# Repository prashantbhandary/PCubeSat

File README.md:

# PocketQube PCB

KiCad schematic and PCB for the electronics of a 1.5U PocketQube educational satellite model.

## Paper
This project is described in a technical report:
**Electronics Design of a Low-Cost 1.5U PocketQube Educational Satellite Model with LoRa Telemetry and Stacked PCBs** — **Prashant Bhandari**, 2026. [Read the paper](https://www.researchgate.net/publication/418425160) · DOI: [10.13140/RG.2.2.14744.84482](https://doi.org/10.13140/RG.2.2.14744.84482)

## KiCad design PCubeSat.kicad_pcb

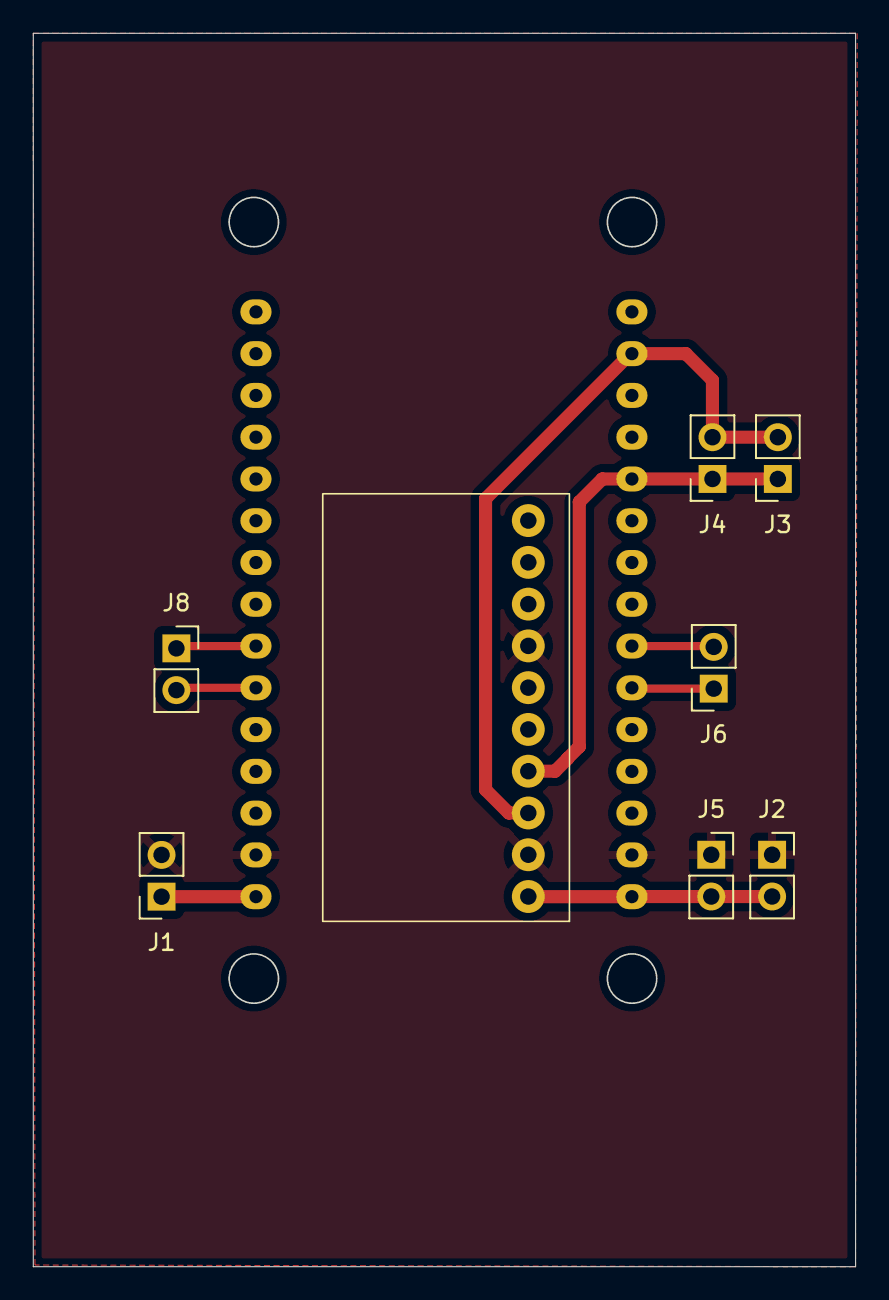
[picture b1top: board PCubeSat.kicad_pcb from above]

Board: 2 copper layers, 50.0 x 75.0 mm, 9 parts (1 on the bottom side), 9 nets.

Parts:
J1, J2, J3, J4, J5, J6, J8: Conn_01x02_Pin; PinSocket_1x02_P2.54mm_Vertical
U1: ESP32-WROOM-32E-N8R2; ESP_Test
U2: mpu9250

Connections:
/3V3: J2.2, J5.2, U1.16 (3V3), U2.1 (VCC)
/GND: J1.2, J2.1, J5.1, U1.14 (GND), U1.17 (GND), U2.2 (GND), U2.7 (AD0)
/IO21: J3.1, J4.1, U1.26 (IO21), U2.4 (SDA)
/IO22: J3.2, J4.2, U1.29 (IO22), U2.3 (SCL)
/VIN: J1.1, U1.15 (VIN)
unnamed: J6.1, U1.21 (IO16)
unnamed: J6.2, U1.22 (IO17)
unnamed: J8.1, U1.9 (IO26)
unnamed: J8.2, U1.10 (IO27)

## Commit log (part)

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2025-11-21 added esp32 and mpu sch, pcb ,3d
